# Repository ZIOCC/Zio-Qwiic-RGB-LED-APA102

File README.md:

# Zio-Qwiic-RGB-LED-APA102

> This product can be available for purchase [here](https://www.smart-prototyping.com/Zio-Qwiic-RGB-LED-APA102).

#### Description

This is a ZIO Qwiic board featuring the incredibly bright and colorful APA102 (5mm x 5mm), SMD addressable RGB LED. The board can be also used as a driver board to control multiple APA102 LEDs , simply connect more APA102 as you want (max. to 100 LEDs), chain them together to the Zio Qwiic RGB LED board. 

We created the board that makes 5050 SMD LED much more accessible and works on I2C interface. Isn’t it awesome? 

The APA102-5050 LED with an integrated control circuit embedded can set the RGB color on a constant current output value and 5-bit (32 level) brightness setting. Pretty challenging to incorporate an IC on an LED right? If you take a glance inside, you can even see the minuscul gold microcontroller and the golden connections to the LED. 

The command to operate the LED is sent to the ATtiny85-20SU that controls the RGB LED.

We also provided the pinout to be able to deal with the LED data and the ATtiny85-20SU!

> Note: You must use a 5V DC Power supply to power the APA102 LED Strips. Watch the the current consumption when using an LED strips, 5V 4A power supply for 0.5m/ 1m and 5V 10A up to 2m (depending on the application)

#### Specification

* Operation Voltage: 3.3V
* Operating Temperature: -40°C - 40°C
* IC: ATTINY85-20SU
* I2C address: 0x22, 0x23 (Default:0x23)
* Dimensions: 25.8 x 28.3mm
* Weight: 2.9g

#### Links

* [LED APA102 Datasheet](http://www.smart-prototyping.com/image/data/2_components/Light/101791%20APA102C%20LED%20Strip/APA102C.pdf)
* [PCB source file and Gerber file](https://github.com/ZIOCC/Zio-Qwiic-RGB-LED-APA102)
* [ATtiny85-20SU Firmware](https://github.com/ZIOCC/Zio-Qwiic-RGB-LED-APA102/tree/master/Firmware/Qwiic_LED_Stick)
* [Testing Code (Sparkfun Qwiic LED Stick Arduino Library master)](https://github.com/sparkfun/SparkFun_Qwiic_LED_Stick_Arduino_Library)

> ###### About Zio
> Zio is a new line of open sourced, compact, and grid layout boards, fully integrated for Arduino and Qwiic ecosystem. Designed ideally for wearables, robotics, small-space limitations or other on the go projects. Check out other awesome Zio products [here](https://www.smart-prototyping.com/Zio).

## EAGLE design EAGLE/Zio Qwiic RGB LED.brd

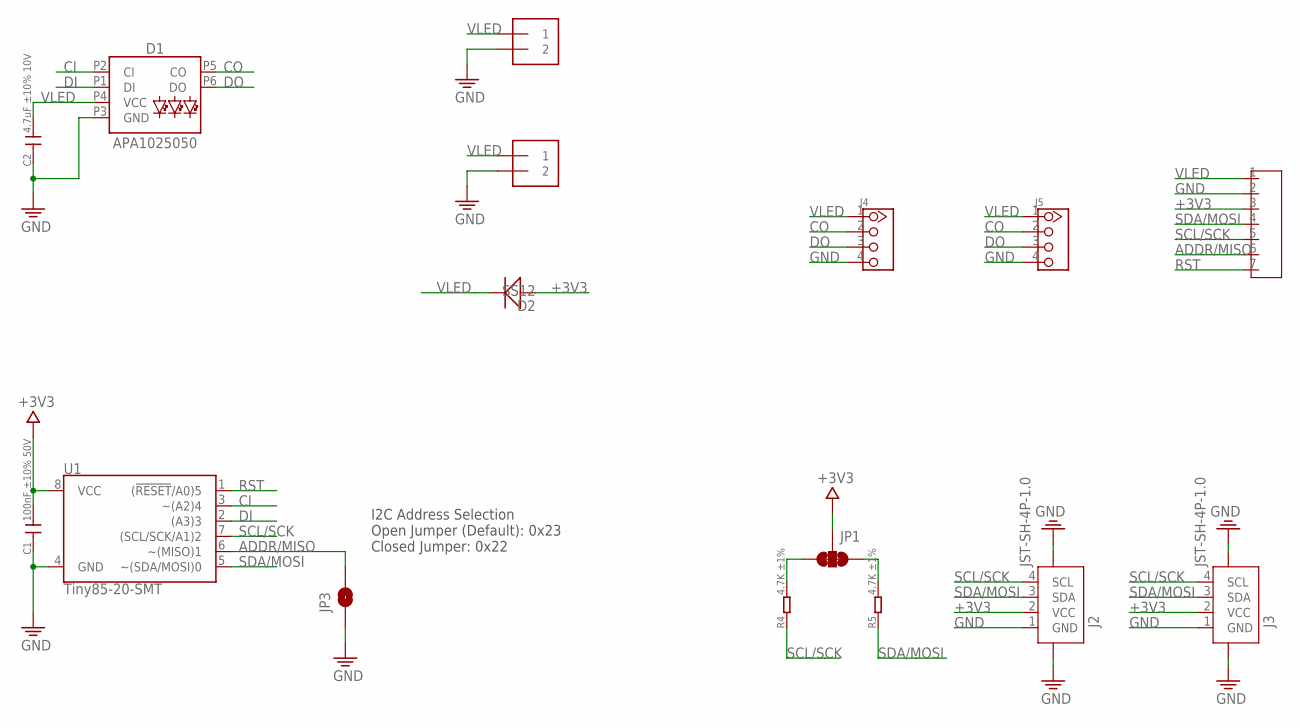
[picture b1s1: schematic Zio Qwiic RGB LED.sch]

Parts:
C1: 100nF ±10% 50V; C0402
C2: 4.7uF ±10% 10V; C0603
D1: APA1025050; APA102-5050
D2: SS12; DO-214AC
J1: HEADER-7P-2.54; 7P-2.54-65/35MIL
J2, J3: JST-SH-4P-1.0; JST-SH-4P
J4: HEADER-4P-2.54-M; 4P-2.54-SMD-M
J5: HEADER-4P-60/35MIL; 4P-65/35MIL
J6, J7: TERMBLOCK_1X2-3.5MM; 1X2-3.5MM
JP1: SMT-JUMPER_3_2-NC_TRACE
JP3: JUMPER-SMT_2_NC_PASTE_SILK; SMT-JUMPER_2_NC_PASTE_SILK
R4, R5: 4.7K ±1%; R0402
U1: Tiny85-20-SMT; SO08-EIAJ_MCU

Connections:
+3V3: C1.2, D2.A (+), J1.3, J2.2 (VCC), J3.2 (VCC), JP1.2, U1.8 (VCC)
ADDR/MISO: J1.6, JP3.2, U1.6 (~(MISO)1)
CI: D1.P2 (CI), U1.3 (~(A2)4)
CO: D1.P5 (CO), J4.2, J5.2
DI: D1.P1 (DI), U1.2 ((A3)3)
DO: D1.P6 (DO), J4.3, J5.3
GND: C1.1, C2.1, D1.P3 (GND), J1.2, J2.1 (GND), J2.NC1 (5), J2.NC2 (6), J3.1 (GND), J3.NC1 (5), J3.NC2 (6), J4.4, J5.4, J6.2, J7.2, JP3.1, U1.4 (GND)
unnamed: JP1.3, R4.2
unnamed: JP1.1, R5.2
RST: J1.7, U1.1 ((!RESET!/A0)5)
SCL/SCK: J1.5, J2.4 (SCL), J3.4 (SCL), R4.1, U1.7 ((SCL/SCK/A1)2)
SDA/MOSI: J1.4, J2.3 (SDA), J3.3 (SDA), R5.1, U1.5 (~(SDA/MOSI)0)
VLED: C2.2, D1.P4 (VCC), D2.C (-), J1.1, J4.1, J5.1, J6.1, J7.1

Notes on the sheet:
I2C Address Selection Open Jumper (Default): 0x23 Closed Jumper: 0x22

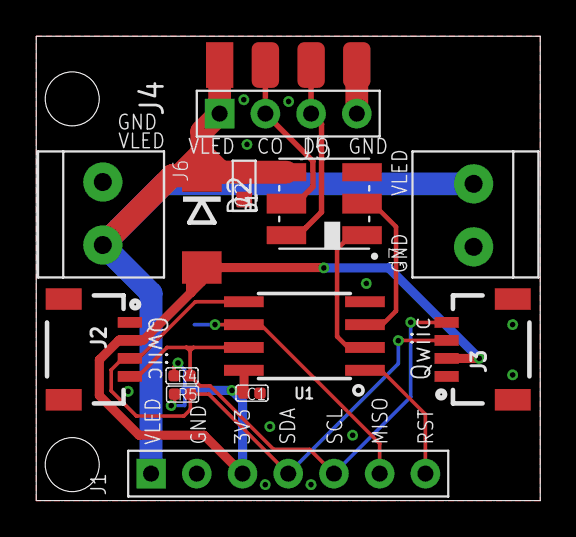
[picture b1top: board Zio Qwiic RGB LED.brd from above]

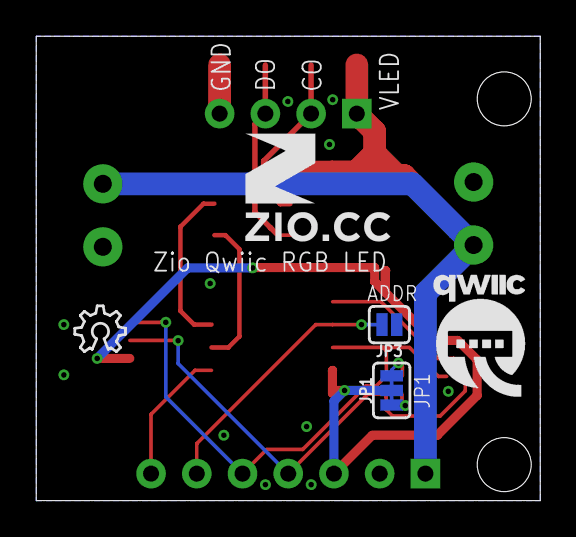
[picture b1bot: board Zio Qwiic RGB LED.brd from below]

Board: 2 copper layers, 28.0 x 25.8 mm, 19 parts (5 on the bottom side), 13 nets.

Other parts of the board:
U$1: QWIIC-LOGO-MEDIUM
U$3: OSHW_6X100_NOTEXT
U$4: 6MM

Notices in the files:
parts and their libraries:
SparkFun-LED: Licensing: Creative Commons ShareAlike 4.0 International - https://creativecommons.org/licenses/by-sa/4.0
